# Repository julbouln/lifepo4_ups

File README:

5V/2A LTC4040 and STM32F042/STM32F070 based Lifepo4 UPS

https://www.analog.com/media/en/technical-documentation/data-sheets/4040fb.pdf
https://www.st.com/resource/en/datasheet/stm32f042k6.pdf

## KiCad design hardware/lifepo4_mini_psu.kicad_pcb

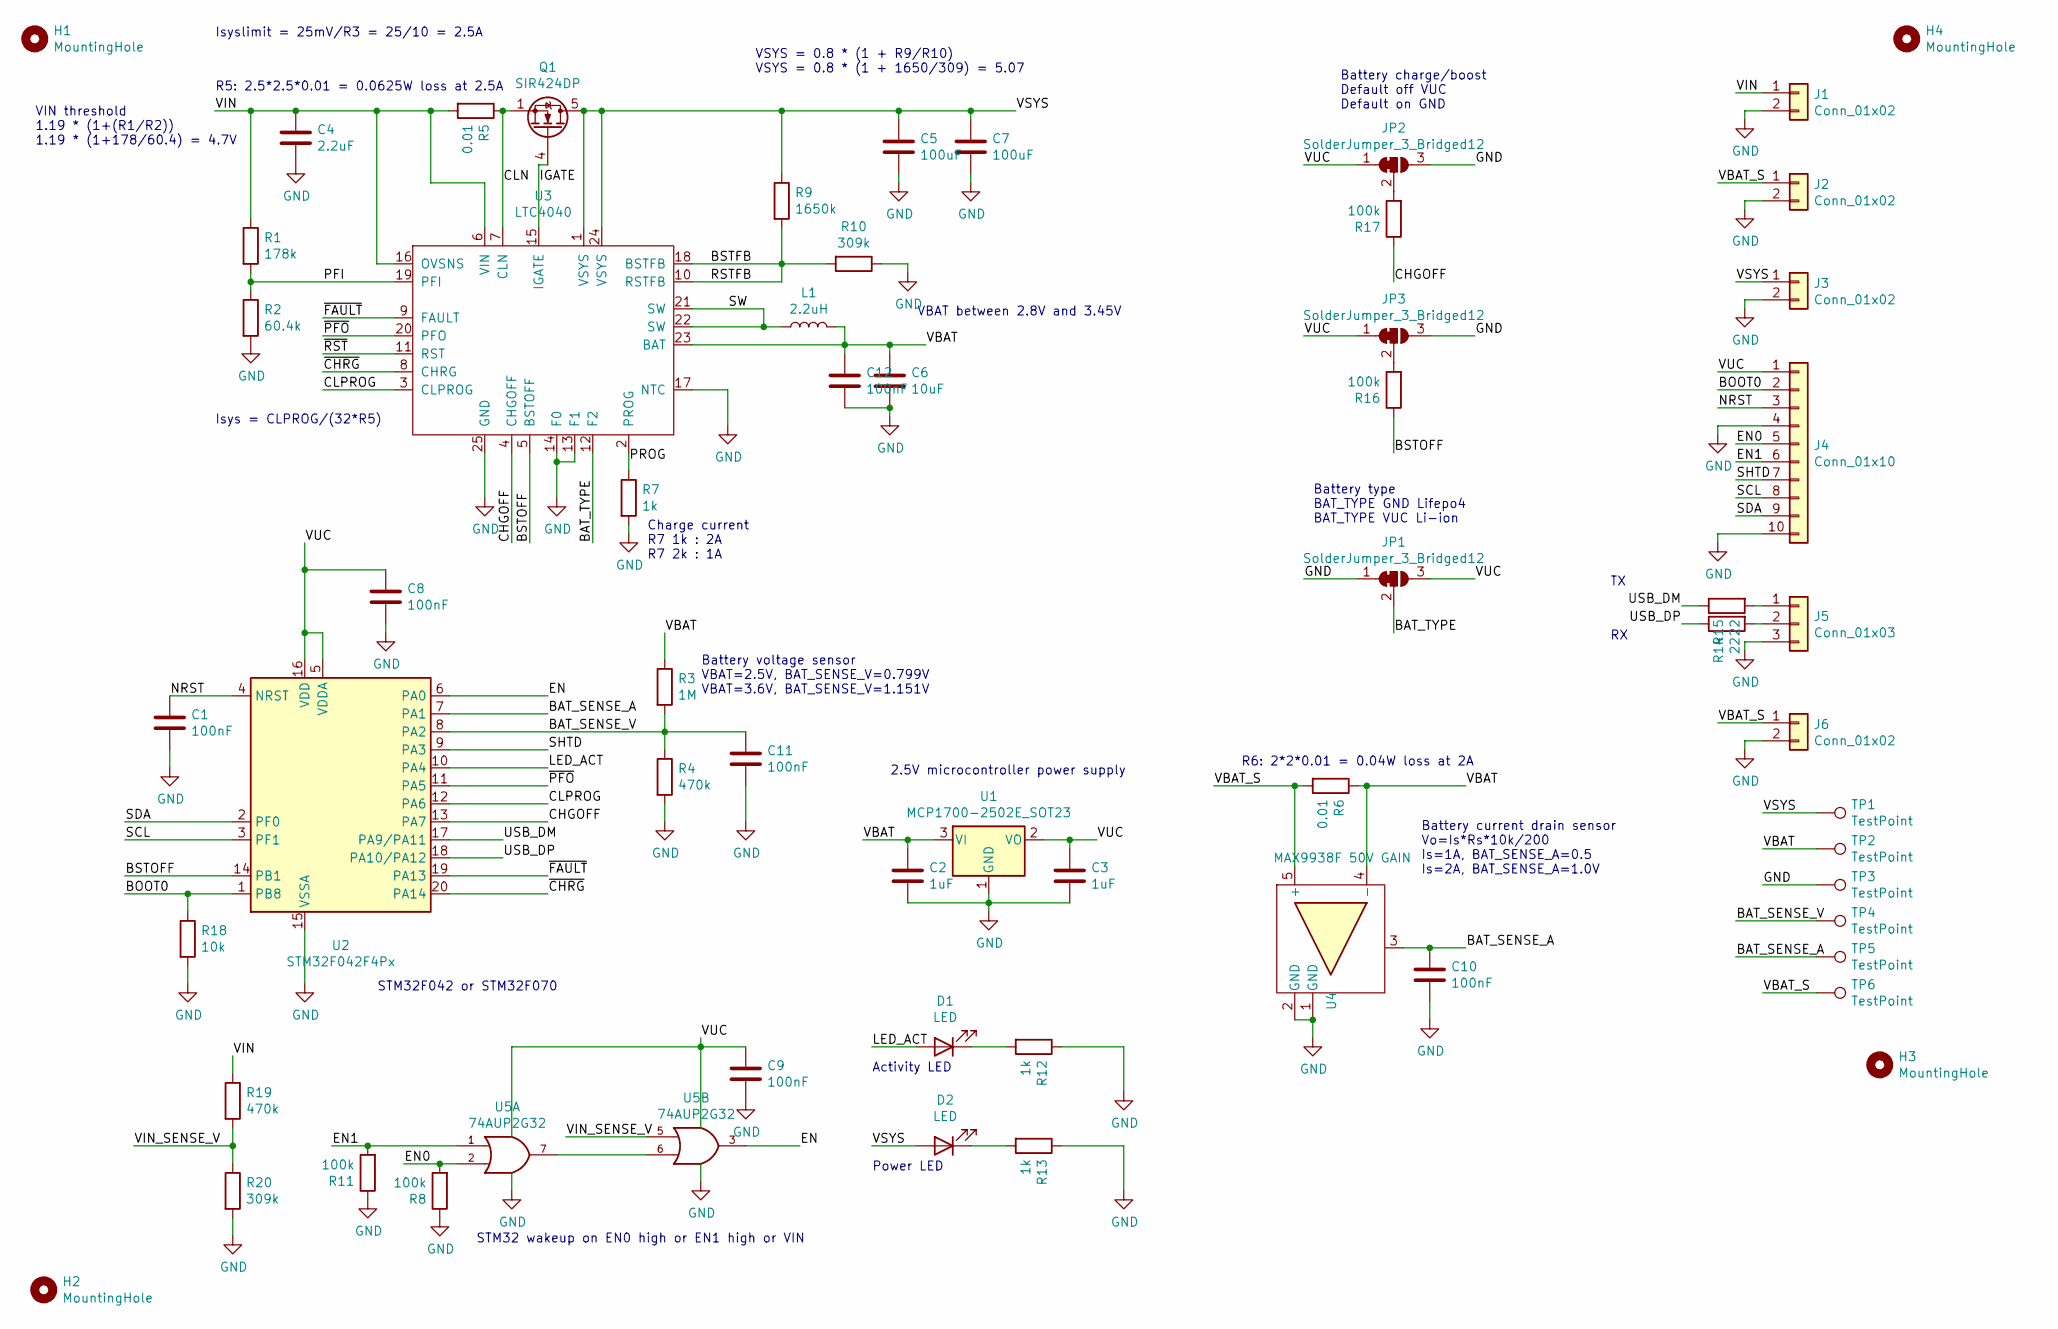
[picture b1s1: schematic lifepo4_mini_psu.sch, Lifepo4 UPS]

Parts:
C1, C8, C9, C10, C11, C12: 100nF; C_0603_1608Metric_Pad1.05x0.95mm_HandSolder
C2, C3: 1uF; C_0603_1608Metric_Pad1.05x0.95mm_HandSolder
C4: 2.2uF; C_0603_1608Metric_Pad1.05x0.95mm_HandSolder
C5, C7: 100uF; C_1210_3225Metric_Pad1.42x2.65mm_HandSolder
C6: 10uF; C_0603_1608Metric_Pad1.05x0.95mm_HandSolder
D1, D2: LED; LED_0603_1608Metric_Pad1.05x0.95mm_HandSolder
H1, H2, H3, H4: MountingHole; MountingHole_2.7mm_M2.5
J1, J2, J3, J6: Conn_01x02; PinHeader_1x02_P2.54mm_Vertical
J4: Conn_01x10; PinHeader_1x10_P2.54mm_Vertical
J5: Conn_01x03; PinHeader_1x03_P2.54mm_Vertical
JP1, JP2, JP3: SolderJumper_3_Bridged12; SolderJumper-3_P1.3mm_Bridged12_RoundedPad1.0x1.5mm
L1: 2.2uH; L_Coilcraft_XAL5030
Q1: SIR424DP; PowerPAK_SO-8_Single
R1: 178k; R_0603_1608Metric_Pad1.05x0.95mm_HandSolder
R2: 60.4k; R_0603_1608Metric_Pad1.05x0.95mm_HandSolder
R3: 1M; R_0603_1608Metric_Pad1.05x0.95mm_HandSolder
R4, R19: 470k; R_0603_1608Metric_Pad1.05x0.95mm_HandSolder
R5, R6: 0.01; R_1206_3216Metric_Pad1.42x1.75mm_HandSolder
R7, R12, R13: 1k; R_0603_1608Metric_Pad1.05x0.95mm_HandSolder
R8, R11, R16, R17: 100k; R_0603_1608Metric_Pad1.05x0.95mm_HandSolder
R9: 1650k; R_0603_1608Metric_Pad1.05x0.95mm_HandSolder
R10, R20: 309k; R_0603_1608Metric_Pad1.05x0.95mm_HandSolder
R14, R15: 22; R_0603_1608Metric_Pad1.05x0.95mm_HandSolder
R18: 10k; R_0603_1608Metric_Pad1.05x0.95mm_HandSolder
TP1, TP2, TP3, TP4, TP5, TP6: TestPoint; TestPoint_THTPad_D1.0mm_Drill0.5mm
U1: MCP1700-2502E_SOT23; SOT-23
U2: STM32F042F4Px; TSSOP-20_4.4x6.5mm_P0.65mm
U3: LTC4040; QFN-24-1EP_4x5mm_P0.5mm_EP2.65x3.65mm
U4: MAX9938F 50V GAIN; SOT-23-5
U5: 74AUP2G32; VSSOP-8_2.3x2mm_P0.5mm

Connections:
/BAT_SENSE_A: C10.1, TP5.1, U2.7 (PA1), U4.3
/BAT_SENSE_V: C11.1, R3.2, R4.1, TP4.1, U2.8 (PA2)
/BAT_TYPE: JP1.2 (C), U3.12 (F2)
/BOOT0: J4.2, R18.1, U2.1 (PB8)
/BSTFB: R9.2, R10.2, U3.10 (RSTFB), U3.18 (BSTFB)
/BSTOFF: R16.1, U2.14 (PB1), U3.5 (BSTOFF)
/CHGOFF: R17.1, U2.13 (PA7), U3.4 (CHGOFF)
/CLN: Q1.1 (S), Q1.2 (S), Q1.3 (S), R5.1, U3.7 (CLN)
/CLPROG: U2.12 (PA6), U3.3 (CLPROG)
/EN: U2.6 (PA0), U5.3
/EN0: J4.5, R8.2, U5.2
/EN1: J4.6, R11.2, U5.1
/IGATE: Q1.4 (G), U3.15 (IGATE)
/LED_ACT: D1.2 (A), U2.10 (PA4)
/NRST: C1.1, J4.3, U2.4 (NRST)
/PFI: R1.2, R2.1, U3.19 (PFI)
/PROG: R7.1, U3.2 (PROG)
/SCL: J4.8, U2.3 (PF1)
/SDA: J4.9, U2.2 (PF0)
/SHTD: J4.7, U2.9 (PA3)
/SW: L1.1, U3.21 (SW), U3.22 (SW)
/USB_DM: R15.1, U2.17 (PA9/PA11)
/USB_DP: R14.1, U2.18 (PA10/PA12)
/VBAT: C2.1, C6.1, C12.1, L1.2, R3.1, R6.1, TP2.1, U1.3 (VI), U3.23 (BAT), U4.4 (-)
/VBAT_S: J2.1, J6.1, R6.2, TP6.1, U4.5 (+)
/VIN: C4.1, J1.1, R1.1, R5.2, R19.1, U3.6 (VIN), U3.16 (OVSNS)
/VIN_SENSE_V: R19.2, R20.1, U5.5
/VSYS: C5.1, C7.1, D2.2 (A), J3.1, Q1.5 (D), R9.1, TP1.1, U3.1 (VSYS), U3.24 (VSYS)
/~CHRG: U2.20 (PA14), U3.8 (CHRG)
/~FAULT: U2.19 (PA13), U3.9 (FAULT)
/~PFO: U2.11 (PA5), U3.20 (PFO)
/~RST: U3.11 (RST)
GND: C1.2, C2.2, C3.2, C4.2, C5.2, C6.2, C7.2, C8.2, C9.2, C10.2, C11.2, C12.2, J1.2, J2.2, J3.2, J4.4, J4.10, J5.3, J6.2, JP1.1 (A), JP2.3 (B), JP3.3 (B), R2.2, R4.2, R7.2, R8.1, R10.1, R11.1, R12.1, R13.1, R18.2, R20.2, TP3.1, U1.1 (GND), U2.15 (VSSA), U3.13 (F1), U3.14 (F0), U3.17 (NTC), U3.25 (GND), U4.1 (GND), U4.2 (GND), U5.4 (GND)
unnamed: D1.1 (K), R12.2
unnamed: D2.1 (K), R13.2
unnamed: J5.1, R15.2
unnamed: J5.2, R14.2
unnamed: JP2.2 (C), R17.2
unnamed: JP3.2 (C), R16.2
unnamed: U5.6, U5.7
VCC: C3.1, C8.1, C9.1, J4.1, JP1.3 (B), JP2.1 (A), JP3.1 (A), U1.2 (VO), U2.5 (VDDA), U2.16 (VDD), U5.8 (VCC)

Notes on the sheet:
Charge current R7 1k : 2A R7 2k : 1A
Isyslimit = 25mV/R3 = 25/10 = 2.5A
VBAT between 2.8V and 3.45V
Isys = CLPROG/(32*R5)
Battery voltage sensor VBAT=2.5V, BAT_SENSE_V=0.799V VBAT=3.6V, BAT_SENSE_V=1.151V
Battery current drain sensor Vo=Is*Rs*10k/200 Is=1A, BAT_SENSE_A=0.5 Is=2A, BAT_SENSE_A=1.0V
Battery charge/boost Default off VUC Default on GND
R6: 2*2*0.01 = 0.04W loss at 2A
R5: 2.5*2.5*0.01 = 0.0625W loss at 2.5A
VIN threshold 1.19 * (1+(R1/R2)) 1.19 * (1+178/60.4) = 4.7V
VSYS = 0.8 * (1 + R9/R10) VSYS = 0.8 * (1 + 1650/309) = 5.07
2.5V microcontroller power supply
STM32 wakeup on EN0 high or EN1 high or VIN
Power LED
Activity LED
Battery type BAT_TYPE GND Lifepo4 BAT_TYPE VUC Li-ion
STM32F042 or STM32F070

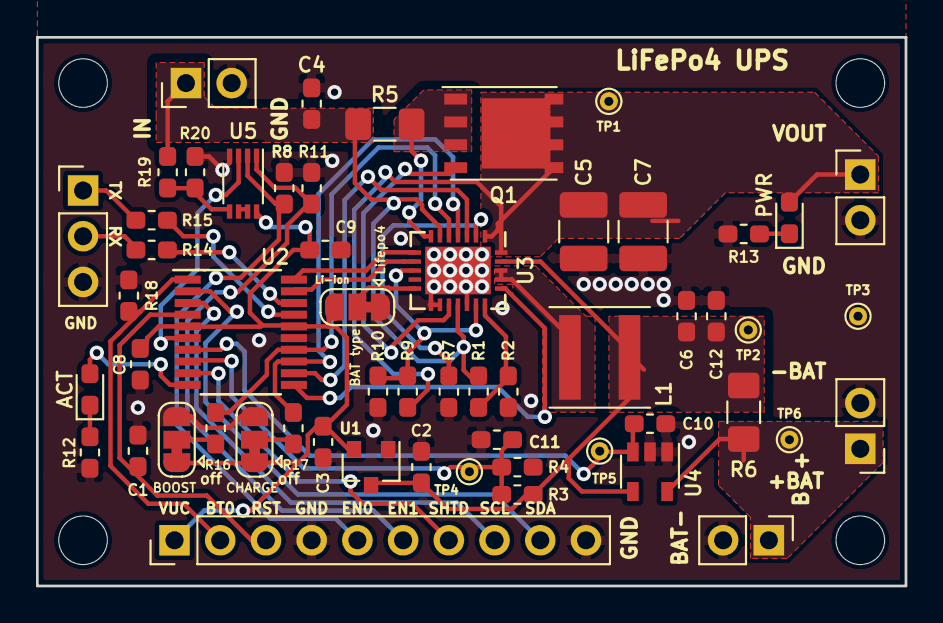
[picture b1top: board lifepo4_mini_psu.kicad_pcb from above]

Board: 2 copper layers, 48.3 x 30.5 mm, 60 parts (0 on the bottom side), 40 nets.

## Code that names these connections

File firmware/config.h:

#ifndef CONFIG_H
#define CONFIG_H

#define I2C_SLAVE_ADDR 0x32

#define TIMER_EXPIRE_MIN 1
#define SHUTDOWN_WAIT_SEC 10

#define EN_PORT GPIOA
#define EN_PIN GPIO0

#define SHUTDOWN_PORT GPIOA
#define SHUTDOWN_PIN GPIO3

#define BOOST_EN_PORT GPIOB
#define BOOST_EN_PIN GPIO1

#define CHARGE_EN_PORT GPIOA
#define CHARGE_EN_PIN GPIO7

#define PWM_PORT_G  GPIOA
#define PWM_PIN_G GPIO4
#define PWM_RCC_G RCC_TIM14
#define PWM_AF_G GPIO_AF4
#define PWM_TIMER_G TIM14
#define PWM_CHAN_G TIM_OC1

#define LED_TIMER TIM2
#define LED_TIMER_RCC RCC_TIM2
#define LED_TIMER_RST RST_TIM2
#define LED_TIMER_NVIC NVIC_TIM2_IRQ
#define led_tim_isr tim2_isr

#define ADC_SAMPLES 100

#define BAT_SENSE_A_PORT GPIOA
#define BAT_SENSE_A_PIN GPIO1

#define BAT_SENSE_V_PORT GPIOA
#define BAT_SENSE_V_PIN GPIO2

#define INP_SENSE_A_PORT GPIOA
#define INP_SENSE_A_PIN GPIO6

#define BAT_CHRG_PORT GPIOA
#define BAT_CHRG_PIN GPIO14

#define BAT_PFO_PORT GPIOA
#define BAT_PFO_PIN GPIO5

#define BAT_FAULT_PORT GPIOA
#define BAT_FAULT_PIN GPIO13

#define USART_PORT GPIOA
#define USART_TX_PIN GPIO9
#define USART_RX_PIN GPIO10


#define I2C_CMD_ENABLE

//#define USB_ENABLE
#define USB_PORT GPIOA
#define USB_DM_PIN GPIO11
#define USB_DP_PIN GPIO12
#define USB_USE_INT 1

#endif

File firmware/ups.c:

#include <libopencm3/stm32/rcc.h>
#include <libopencm3/stm32/gpio.h>
#include <libopencm3/stm32/rtc.h>
#include <libopencm3/stm32/exti.h>
#include <libopencm3/stm32/flash.h>

#include <libopencm3/stm32/timer.h>

#include <libopencm3/stm32/crs.h>
#include <libopencm3/stm32/syscfg.h>

#include <libopencm3/cm3/nvic.h>

#include <libopencm3/cm3/systick.h>

#include "config.h"
#include "usb.h"
#include "usart.h"
#include "i2c.h"
#include "rtc.h"
#include "pwm.h"
#include "adc.h"
#include "power.h"
#include "cmd.h"

void gpio_setup(void);
void gpio_irq_setup(void);
void rcc_clock_setup_in_hsi_out_8mhz(void);
void clock_setup(void);
void led_set_mode(uint8_t mode);
void led_set_luminance(float l);

static inline __attribute__((always_inline)) void __WFI(void)
{
	__asm volatile("wfi");
}

void gpio_setup(void)
{
	/* WAKE UP/EN pin */
	gpio_mode_setup(EN_PORT, GPIO_MODE_INPUT, GPIO_PUPD_PULLDOWN, EN_PIN);

	/* SHUTDOWN pin */
	gpio_mode_setup(SHUTDOWN_PORT, GPIO_MODE_INPUT, GPIO_PUPD_NONE, SHUTDOWN_PIN);

	/* POWER pin */
	gpio_mode_setup(BOOST_EN_PORT, GPIO_MODE_OUTPUT, GPIO_PUPD_NONE, BOOST_EN_PIN);

	/* UPS POWER pin */
	gpio_mode_setup(CHARGE_EN_PORT, GPIO_MODE_OUTPUT, GPIO_PUPD_NONE, CHARGE_EN_PIN);

	/* BATTERY SENSE V pin */
	gpio_mode_setup(BAT_SENSE_V_PORT, GPIO_MODE_ANALOG, GPIO_PUPD_NONE, BAT_SENSE_V_PIN);

	/* BATTERY SENSE A pin */
	gpio_mode_setup(BAT_SENSE_A_PORT, GPIO_MODE_ANALOG, GPIO_PUPD_NONE, BAT_SENSE_A_PIN);

	/* INPUT SENSE A pin */
	gpio_mode_setup(INP_SENSE_A_PORT, GPIO_MODE_ANALOG, GPIO_PUPD_NONE, INP_SENSE_A_PIN);

	/* PFO pin */
	/* LOW = on battery, HIGH = on charger */
	gpio_mode_setup(BAT_PFO_PORT, GPIO_MODE_INPUT, GPIO_PUPD_PULLUP, BAT_PFO_PIN);

	/* FAULT pin */
	/* LOW = fault, HIGH = OK */
	gpio_mode_setup(BAT_FAULT_PORT, GPIO_MODE_INPUT, GPIO_PUPD_PULLUP, BAT_FAULT_PIN);

	/* CHRG pin */
	/* LOW = charging, HIGH = not charging */
	gpio_mode_setup(BAT_CHRG_PORT, GPIO_MODE_INPUT, GPIO_PUPD_PULLUP, BAT_CHRG_PIN);
}

// WAKE UP pin and ALIVE pin should postpone shut down via IRQ
void gpio_irq_setup()
{
	// EXTI0_1 for WAKE UP interrupt
	exti_select_source(EXTI0, GPIOA);
	exti_set_trigger(EXTI0, EXTI_TRIGGER_RISING);
	exti_enable_request(EXTI0);
	nvic_enable_irq(NVIC_EXTI0_1_IRQ);

	// EXTI4_15 for ALIVE interrupt
	exti_select_source(EXTI5, GPIOA);
	exti_set_trigger(EXTI5, EXTI_TRIGGER_RISING);
	exti_enable_request(EXTI5);
	nvic_enable_irq(NVIC_EXTI4_15_IRQ);
}

void flash_prefetch_buffer_enable(void)
{
	FLASH_ACR |= FLASH_ACR_PRFTBE;
}

void rcc_clock_setup_in_hsi_out_8mhz(void)
{
	rcc_osc_on(RCC_HSI);
	rcc_wait_for_osc_ready(RCC_HSI);
	rcc_set_sysclk_source(RCC_HSI);

	rcc_set_hpre(RCC_CFGR_HPRE_NODIV);
	rcc_set_ppre(RCC_CFGR_PPRE_NODIV);

	flash_prefetch_buffer_enable();
	flash_set_ws(FLASH_ACR_LATENCY_024_048MHZ);

	/* 8MHz * 2 / 2 = 8MHz */
	rcc_set_pll_multiplication_factor(RCC_CFGR_PLLMUL_MUL2);
	rcc_set_pll_source(RCC_CFGR_PLLSRC_HSI_CLK_DIV2);

	rcc_osc_on(RCC_PLL);
	rcc_wait_for_osc_ready(RCC_PLL);
	rcc_set_sysclk_source(RCC_PLL);

	rcc_apb1_frequency = 8000000;
	rcc_ahb_frequency = 8000000;
}

void clock_setup(void)
{

#ifdef USB_ENABLE
	rcc_clock_setup_in_hsi48_out_48mhz();
	rcc_periph_clock_enable(RCC_SYSCFG_COMP);
	SYSCFG_CFGR1 |= SYSCFG_CFGR1_PA11_PA12_RMP;
	crs_autotrim_usb_enable();
	rcc_set_usbclk_source(RCC_HSI48);
#else
	rcc_clock_setup_in_hsi_out_48mhz();
//	rcc_clock_setup_in_hsi_out_8mhz();
#endif

	rcc_periph_clock_enable(RCC_GPIOA);
	rcc_periph_clock_enable(RCC_GPIOB);
	rcc_periph_clock_enable(RCC_RTC);
	rcc_periph_clock_enable(RCC_PWR);
	rcc_periph_clock_enable(RCC_ADC);

	/* enable rtc unlocking */
	pwr_disable_backup_domain_write_protect();
}

/* PWM */

uint8_t led_enabled;

uint8_t cur_led_mode = 0;
uint16_t cur_led_oc = 0;
int cur_led_dir = 1;

float led_lum = 1.0;

void led_set_mode(uint8_t mode)
{
	if (led_enabled)
	{
		if (mode != cur_led_mode)
		{
			cur_led_oc = 0;
			cur_led_mode = mode;
		}
	} else {
		cur_led_oc = 0;
		cur_led_mode = LED_MODE_OFF;
	}
}

void led_set_luminance(float l)
{
	led_lum = l;
}

// FIXME: does not work
void led_enable()
{
	led_enabled = 1;
}

// FIXME: does not work
void led_disable()
{
	led_enabled = 0;
}

/* POWER */

int power_down_event;
bool started;

float cur_bat_v = 0;
float cur_bat_a = 0;
float cur_inp_a = 0;

/* IRQ */

void led_tim_isr(void)
{
	uint16_t led_oc;
	if (timer_get_flag(LED_TIMER, TIM_SR_CC1IF))
	{
		/* Clear compare interrupt flag. */
		timer_clear_flag(LED_TIMER, TIM_SR_CC1IF);

		switch (cur_led_mode)
		{
		case LED_MODE_OFF:
			cur_led_oc = 0;
			led_oc = 0;
			break;
		case LED_MODE_SOFT_BLINK:
			if (cur_led_dir)
			{
				if (cur_led_oc < LED_MAX_OC)
					cur_led_oc += PWM_INCR;
				else
					cur_led_dir = 0;
			}
			else
			{
				if (cur_led_oc > 0)
					cur_led_oc -= PWM_INCR;
				else
					cur_led_dir = 1;
			}
			led_oc = cur_led_oc;

			break;
		case LED_MODE_ON:
			cur_led_oc = LED_MAX_OC + 1;
			led_oc = LED_MAX_OC + 1;
			break;
		case LED_MODE_HARD_BLINK:
			if (cur_led_oc < LED_MAX_OC / 2)
			{
				if ((cur_led_oc / 16) % 2)
					led_oc = LED_MAX_OC;
				else
					led_oc = 0;
			}
			else
			{
				led_oc = 0;
			}
			cur_led_oc++;
			if (cur_led_oc > LED_MAX_OC)
				cur_led_oc = 0;
			break;
		default:
			cur_led_oc = 0;
			led_oc = 0;
			break;
		}

		led_pwm_set_dc(PWM_TIMER_G, PWM_CHAN_G, (int)((float)led_oc * led_lum));
	}
	else
	{
		led_pwm_set_dc(PWM_TIMER_G, PWM_CHAN_G, 0);
	}
}

void rtc_isr(void)
{
	started = false;
	//wait(1000);
	power_down_event = 1;
	rtc_disable_alarm();
	exti_reset_request(EXTI17);
}

void exti0_1_isr(void)
{
	power_down_postpone();
	exti_reset_request(EXTI0);
}

void exti4_15_isr(void)
{
	started = true;
	power_down_postpone();
	exti_reset_request(EXTI5);
}

/* systick */

/* Called when systick fires */
void sys_tick_handler(void)
{
	power_down_check_postpone();

	if (power_down_event > 0)
	{
		// clear shutdown pin : will be shuted down in SHUTDOWN_WAIT_SEC
		gpio_clear(SHUTDOWN_PORT, SHUTDOWN_PIN);

		led_set_mode(LED_MODE_HARD_BLINK);

		if (power_down_event == SHUTDOWN_WAIT_SEC)
		{
			rcc_disable_rtc_clock();
			exti_disable_request(EXTI17);
			nvic_disable_irq(NVIC_RTC_IRQ);
			power_down();
		}
		power_down_event++;
	}
	else
	{
		if (!gpio_get(BAT_CHRG_PORT, BAT_CHRG_PIN))
			led_set_mode(LED_MODE_SOFT_BLINK);
		else
			led_set_mode(LED_MODE_ON);
	}

	cur_bat_v = bat_sense_v();
	cur_bat_a = bat_sense_a();
	cur_inp_a = inp_sense_a();
}

/*
 * Set up timer to fire every x milliseconds
 * This is a unusual usage of systick, be very careful with the 24bit range
 * of the systick counter!  You can range from 1 to 2796ms with this.
 */
static void systick_setup(int xms)
{
	/* div8 per ST, stays compatible with M3/M4 parts, well done ST */
	systick_set_clocksource(STK_CSR_CLKSOURCE_EXT);
	/* clear counter so it starts right away */
	STK_CVR = 0;

	systick_set_reload(rcc_ahb_frequency / 8 / 1000 * xms);
	systick_counter_enable();
	systick_interrupt_enable();
}

int main(void)
{
	started = false;
	cur_bat_v = 0.0;
	cur_bat_a = 0.0;
	clock_setup();
	rtc_setup();
	gpio_setup();
	gpio_irq_setup();
	adc_setup();
#ifdef USB_ENABLE
	usb_setup();
#else
	usart_setup();
#endif

#ifdef I2C_CMD_ENABLE
	i2c_slave_setup(I2C_SLAVE_ADDR);
#endif

	led_pwm_init(PWM_RCC_G, PWM_TIMER_G);
	led_pwm_setup(PWM_TIMER_G, PWM_CHAN_G, PWM_PORT_G, PWM_PIN_G, PWM_AF_G, TIM_OCM_PWM2);
	//led_set_luminance(0.5);
	led_timer_setup();

	led_enable();
	led_set_mode(LED_MODE_OFF);

	/* enable rtc irq */
	nvic_enable_irq(NVIC_RTC_IRQ);
	nvic_set_priority(NVIC_RTC_IRQ, 1);

	/* EXTI line 17 is connected to the RTC Alarm event */
	exti_set_trigger(EXTI17, EXTI_TRIGGER_RISING);
	exti_enable_request(EXTI17);

	power_down_event = 0;
	power_up();
	power_down_postpone();

	systick_setup(1000);

	while (1)
	{
		__WFI();
	}

	/* should not be here */
}

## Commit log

2020-08-30 add libopencm3 submodule
2020-08-30 fix wakeup + cleanup
2021-10-16 improve firmware
